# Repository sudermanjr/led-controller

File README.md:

# LED Controller

This is a project to control NeoPixel lights with a PiZeroW and golang

## Usage

`led-controller help`

## Homekit

`led-controller homekit` will start this as a homekit device. Check the help for options, specifically the homekit pin. The homekit device will work with color and brightness controls once registered.

## Dashboard

Currently under heavy development. The dashboard will allow viewing and controlling the neopixel strip.

## Building your Pi Controller

In the [pi-builder](pi-builder) directory is the cloud-init for building my pi image using Hypriot. I have encrypted the cloud-init.yaml file using sops and pgp since it contains secrets. There's not much to this file, so it should be easy to re-create on your own if you like.

## Compiling

This is cross-compiled for the Raspberry Pi using the instructions in the rpi-ws281x repository. This utilizes a build container that is based on the [Balena Golang Image](https://registry.hub.docker.com/r/balenalib/raspberry-pi-golang). If you are using a different Pi, you will want to change the base image in the [Dockerfile](Dockerfile)

The build commands are in the [Makefile](Makefile). You can `make build` to build the Docker container and then use that to build the binary for the Pi. At the end it will show the output of `file led-controller` to verify the type of the binary.

The build will also create a local `.tmp` directory for storing build cache so that subsequent builds are much much faster.

Another word of caution: This container build will utilize your local GOPATH and GOCACHE so that it doesn't have to download every package every time.

## References

- golang library: https://github.com/rpi-ws281x/rpi-ws281x-go
- Pi Image Builder: https://github.com/hypriot/image-builder-rpi

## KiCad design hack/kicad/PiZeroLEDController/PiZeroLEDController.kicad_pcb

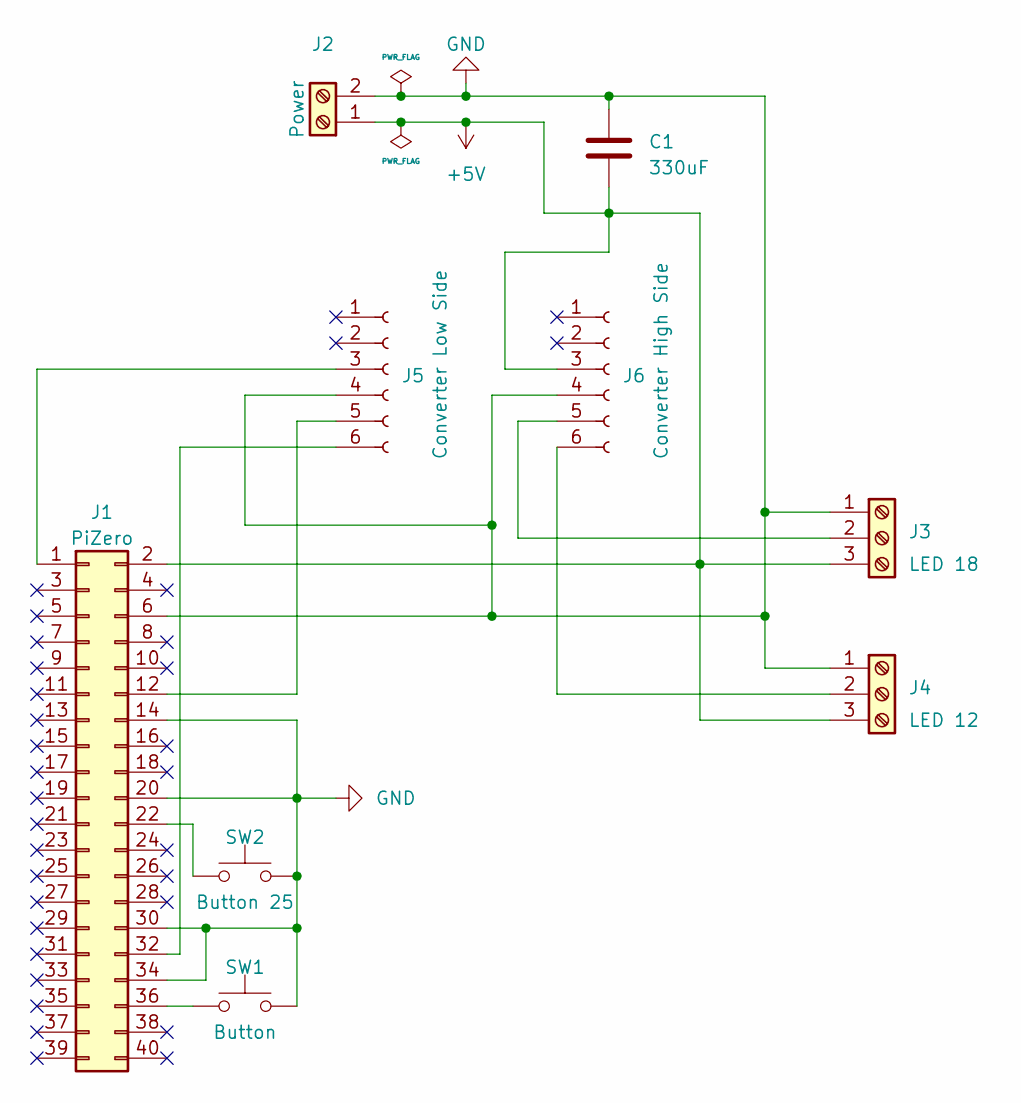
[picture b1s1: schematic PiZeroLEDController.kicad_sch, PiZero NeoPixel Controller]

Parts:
C1: 330uF; CP_Radial_D10.0mm_P5.00mm
J1: PiZero; PinSocket_2x20_P2.54mm_Vertical
J2: Power; TerminalBlock_TE_282834-2_1x02_P2.54mm_Horizontal
J3: LED 18; TerminalBlock_TE_282834-3_1x03_P2.54mm_Horizontal
J4: LED 12; TerminalBlock_TE_282834-3_1x03_P2.54mm_Horizontal
J5: Converter Low Side; PinSocket_1x06_P2.54mm_Vertical
J6: Converter High Side; PinSocket_1x06_P2.54mm_Vertical
SW1: Button; SW_PUSH_6mm_H9.5mm
SW2: Button 25; SW_PUSH_6mm_H9.5mm

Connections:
+5V: C1.1, J1.2, J2.1, J3.3, J4.3, J6.3
GND: C1.2, J1.6, J1.14, J1.20, J1.30, J1.34, J2.2, J3.1, J4.1, J5.4, J6.4, SW1.2, SW2.2
unnamed: J1.1, J5.3
unnamed: J1.12, J5.5
unnamed: J1.22, SW2.1
unnamed: J1.32, J5.6
unnamed: J1.36, SW1.1
unnamed: J3.2, J6.5
unnamed: J4.2, J6.6

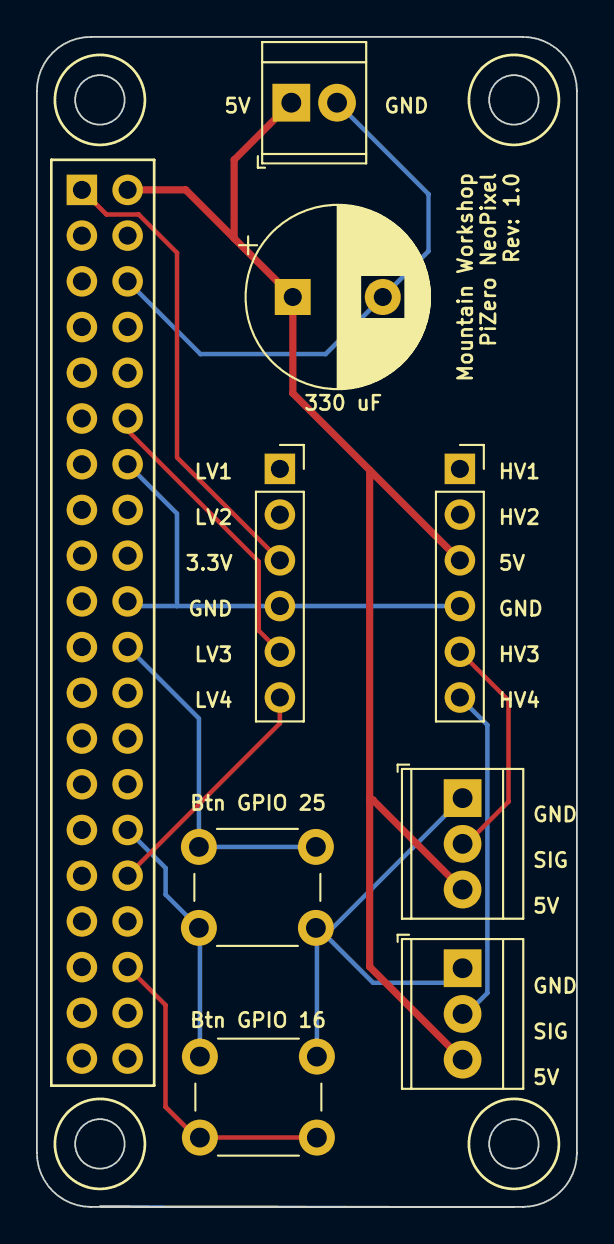
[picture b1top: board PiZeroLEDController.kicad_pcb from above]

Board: 2 copper layers, 30.0 x 65.0 mm, 9 parts (1 on the bottom side), 9 nets.

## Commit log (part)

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2020-01-18 working build using docker for cross compiling
2020-01-18 Rename
2020-01-18 Small tweaks
2020-01-18 Fixing wpa file
2020-01-18 fixing flash process with sops
2020-01-18 working makefile to flash card. remove binary. pre-commit
2020-01-18 Adding readme
2020-01-18 More readme. License
2020-01-18 Fixing cloud init encryption/decryption process
2020-01-18 More fixes to cloud init
2020-01-18 WOrking cloud init
2020-01-18 Enhancements to color handling
2020-01-18 making a CLI
2020-01-19 Working cross-compile using go modules, go 1.12, and cobra
2020-01-19 More flags. Setting some stuff up for future
2020-01-19 ignore
2020-01-19 more flags for demo program
2020-01-19 Adding an on command. Restructuring colors
2020-01-19 Renaming for consistency
2020-01-19 Changing demo defaults
2020-01-19 Added a fade command for the LEDs. Reorganized the led initialization to repeat less code. Renamed some stuff to be more clear.
2020-01-19 Fixing ramp. Logging more homekit actions
2020-01-19 Writing some tests. Scaling function implemented. Ramps are fixed
2020-01-19 Adding a ton of logging
2020-01-19 Using fade everywhere
2020-01-19 Fixing the magic numbers
2020-01-19 Fixing bug where color was turning off lights before fade. Setting up build cache locally to speed up builds. Note in README.
2020-01-19 usage in readme
2020-01-20 Adding color library. Added a gradient to demo. Testing for color usage
2020-01-20 removing unnecessary variable passing between functions
2020-01-20 doing the same for brightness. unnecessary parameters are removed
2020-01-20 Colors working with homekit
2020-01-20 Adding circle yaml
2020-01-20 moving code to separate packages for ease of use
2020-01-20 Reorganizing into packages. Much nicer organization now.
2020-01-20 Working out the bugs with the re-org
2020-01-20 Separating code into packages (#2)
    * Reorganizing into packages. Much nicer organization now.
2020-01-20 Trying out a build inside of Circle
2020-01-20 Build requires test. Use executor instead of docker
2020-01-20 creating specific build for Circle
2020-01-20 error in Makefile for circle
2020-01-20 trying to scale the saturation to match homekit and colorful
2020-01-20 removing circle arm build for now
2020-01-20 Accidental copy on license. Fixing
2020-01-20 license
2020-01-21 Adding a dashboard and using pkger for static files
2020-01-21 Updating readme
2020-01-21 Adding a dashboard (#3)
    * Adding a dashboard and using pkger for static files
2020-01-21 logging improvements in LED settings
2020-01-21 readme updates
2020-01-21 Adding a demo button and backend support
2020-01-21 no delay in control
2020-01-21 Fixing demo
2020-01-21 Adding a demo button and backend support (#8)
    * Adding a demo button and backend support
2020-01-22 Fixing a bug with the ON command
2020-01-25 add stylemark to project
2020-01-25 define lang on html
    for accessibility! https://developer.mozilla.org/en-US/docs/Web/HTML/Element/html
2020-01-25 add make command for running dashboard
    so i don't forget it while i'm learning
2020-01-25 card styling first pass, add label elements
2020-01-25 input and button styling
2020-01-26 add basic link styling
    so they're actually visible because purple on this background doesn't work at all
2020-02-01 First pass at basic styling (#9)
    * add stylemark to project
    * define lang on html
    for accessibility! https://developer.mozilla.org/en-US/docs/Web/HTML/Element/html
    * add make command for running dashboard
    so i don't forget it while i'm learning
    * add first pass at fonts and colors
2020-02-20 new color palette. neumorphic shadows
2020-02-20 new color palette. neumorphic shadows (#11)
2020-02-20 use color picker instead of text input. remove excess padding
2020-02-20 convert brightness inputs to sliders
    part of #6
2020-02-20 add missing demo fields. set min and max
2020-02-23 add missing demo fields. set min and max (#14)
2020-02-23 use color picker instead of text input. remove excess padding (#12)
2020-02-23 Adding lcd screen support
2020-02-23 Adding CLI options for the LCD screen setup
2020-02-23 More functions for screen display
2020-02-23 Turning off screen while I wait for shipping
2020-02-23 More scren functions. enhaced demo
2020-02-23 Signal handling groundwork
2020-02-23 Screen display
2020-02-23 Updating backed for new UI. Basic LCD screen support
2020-02-23 Consolidate dashboard + homekit. Add LCD screen support (#10)
    * Adding lcd screen support
    * Adding CLI options for the LCD screen setup
    * Signal handling groundwork
    * Turning off screen while I wait for shipping
    * More functions for screen display
    * More scren functions. enhaced demo
2020-02-23 Moving brightness scaling function to utils. Update dashboard to use it.
2020-02-23 Moving brightness scaling function to utils. Update dashboard to use it. (#15)
2020-07-19 Bump lodash from 4.17.15 to 4.17.19
    Bumps [lodash](https://github.com/lodash/lodash) from 4.17.15 to 4.17.19.
    - [Release notes](https://github.com/lodash/lodash/releases)
    - [Commits](https://github.com/lodash/lodash/compare/4.17.15...4.17.19)
2020-07-20 Bump lodash from 4.17.15 to 4.17.19 (#16)
    Bumps [lodash](https://github.com/lodash/lodash) from 4.17.15 to 4.17.19.
    - [Release notes](https://github.com/lodash/lodash/releases)
    - [Commits](https://github.com/lodash/lodash/compare/4.17.15...4.17.19)
2020-08-13 remove usage
2020-08-13 change readme
2021-03-31 Bump y18n from 3.2.1 to 3.2.2
    Bumps [y18n](https://github.com/yargs/y18n) from 3.2.1 to 3.2.2.
    - [Release notes](https://github.com/yargs/y18n/releases)
    - [Changelog](https://github.com/yargs/y18n/blob/master/CHANGELOG.md)
    - [Commits](https://github.com/yargs/y18n/commits)
2021-05-08 Bump handlebars from 4.7.2 to 4.7.7
    Bumps [handlebars](https://github.com/wycats/handlebars.js) from 4.7.2 to 4.7.7.
    - [Release notes](https://github.com/wycats/handlebars.js/releases)
    - [Changelog](https://github.com/handlebars-lang/handlebars.js/blob/master/release-notes.md)
    - [Commits](https://github.com/wycats/handlebars.js/compare/v4.7.2...v4.7.7)
2021-05-11 Bump lodash from 4.17.19 to 4.17.21
    Bumps [lodash](https://github.com/lodash/lodash) from 4.17.19 to 4.17.21.
    - [Release notes](https://github.com/lodash/lodash/releases)
    - [Commits](https://github.com/lodash/lodash/compare/4.17.19...4.17.21)
2021-08-11 Bump path-parse from 1.0.6 to 1.0.7
    Bumps [path-parse](https://github.com/jbgutierrez/path-parse) from 1.0.6 to 1.0.7.
    - [Release notes](https://github.com/jbgutierrez/path-parse/releases)
    - [Commits](https://github.com/jbgutierrez/path-parse/commits/v1.0.7)
    ---
    updated-dependencies:
    - dependency-name: path-parse
2021-11-13 Update deps and go version. Move to embed from pkger
2021-11-13 More updates. Fix build process
2021-11-13 tidy
2021-11-13 update circle
2021-11-13 Pin debian version
2021-11-13 build in circle
2021-11-13 use cimg golang
2021-11-13 fix circle
2021-11-13 update cirlce
2021-11-13 Verify experimental features
2021-11-13 update docker
2021-11-13 fix help command
2021-11-13 armv6
2021-11-13 Disable build in circle
2021-11-13 Update versions (#23)
    * Update deps and go version. Move to embed from pkger
    * More updates. Fix build process
    * tidy
    * update circle
    * Pin debian version
    * build in circle
2021-11-13 Fix pathing for static assets
2022-04-09 Bump moment from 2.24.0 to 2.29.2
    Bumps [moment](https://github.com/moment/moment) from 2.24.0 to 2.29.2.
    - [Release notes](https://github.com/moment/moment/releases)
    - [Changelog](https://github.com/moment/moment/blob/develop/CHANGELOG.md)
    - [Commits](https://github.com/moment/moment/compare/2.24.0...2.29.2)
    ---
    updated-dependencies:
2022-07-07 Bump moment from 2.24.0 to 2.29.4
    Bumps [moment](https://github.com/moment/moment) from 2.24.0 to 2.29.4.
    - [Release notes](https://github.com/moment/moment/releases)
    - [Changelog](https://github.com/moment/moment/blob/develop/CHANGELOG.md)
    - [Commits](https://github.com/moment/moment/compare/2.24.0...2.29.4)
    ---
    updated-dependencies:
2022-11-23 Bump engine.io and browser-sync
    Bumps [engine.io](https://github.com/socketio/engine.io) and [browser-sync](https://github.com/BrowserSync/browser-sync). These dependencies needed to be updated together.
    Updates `engine.io` from 3.2.1 to 6.2.1
    - [Release notes](https://github.com/socketio/engine.io/releases)
    - [Changelog](https://github.com/socketio/engine.io/blob/main/CHANGELOG.md)
    - [Commits](https://github.com/socketio/engine.io/compare/3.2.1...6.2.1)
    Updates `browser-sync` from 2.26.7 to 2.27.10
2022-12-05 Bump decode-uri-component from 0.2.0 to 0.2.2
    Bumps [decode-uri-component](https://github.com/SamVerschueren/decode-uri-component) from 0.2.0 to 0.2.2.
    - [Release notes](https://github.com/SamVerschueren/decode-uri-component/releases)
    - [Commits](https://github.com/SamVerschueren/decode-uri-component/compare/v0.2.0...v0.2.2)
    ---
    updated-dependencies:
    - dependency-name: decode-uri-component
2023-02-18 initial button watcher in place
2023-02-18 refactor logging
2023-02-18 Logging complete
2023-02-18 Move to Chi
2023-02-18 log button presses better
2023-02-18 put the root handler back
2023-02-19 Fixing router
2023-02-19 systemd unit file for cloud init and fix router
2023-02-19 button wired up
2023-02-19 Button turns things on and off now
2023-02-19 Way too much logging
2023-02-19 don't fade with button
2023-02-19 Bump ini from 1.3.5 to 1.3.8
    Bumps [ini](https://github.com/npm/ini) from 1.3.5 to 1.3.8.
    - [Release notes](https://github.com/npm/ini/releases)
    - [Changelog](https://github.com/npm/ini/blob/main/CHANGELOG.md)
    - [Commits](https://github.com/npm/ini/compare/v1.3.5...v1.3.8)
    ---
    updated-dependencies:
2023-02-19 Bump tar from 4.4.13 to 4.4.19
    Bumps [tar](https://github.com/npm/node-tar) from 4.4.13 to 4.4.19.
    - [Release notes](https://github.com/npm/node-tar/releases)
    - [Changelog](https://github.com/isaacs/node-tar/blob/main/CHANGELOG.md)
    - [Commits](https://github.com/npm/node-tar/compare/v4.4.13...v4.4.19)
    ---
    updated-dependencies:
2023-02-19 Bump axios and browser-sync
    Bumps [axios](https://github.com/axios/axios) and [browser-sync](https://github.com/BrowserSync/browser-sync). These dependencies needed to be updated together.
    Updates `axios` from 0.19.0 to 0.21.4
    - [Release notes](https://github.com/axios/axios/releases)
    - [Changelog](https://github.com/axios/axios/blob/v0.21.4/CHANGELOG.md)
    - [Commits](https://github.com/axios/axios/compare/v0.19.0...v0.21.4)
    Updates `browser-sync` from 2.26.7 to 2.27.11
2023-02-19 update dependencies
2023-02-19 roll back the hc dependency
2023-02-20 update the button to be more specific
2023-02-22 Set default button press color
2023-02-22 add power button to UI
2023-02-22 fix gradient steps
2023-02-22 better demo default
2023-02-26 pi-builder is no longer useful now that hypriot is gone
2023-02-26 ansible playbook
2023-02-26 Update default max brightness
2023-02-26 add homekit pin to each inventory item
2023-02-26 ansible to latest version
2023-02-26 update ansible version
2023-02-28 Add kicad files
2023-02-28 remove circle
